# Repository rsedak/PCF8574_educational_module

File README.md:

[Croatian version](README_HR-HR.md).

Introduction
============

Purpose of PCF8574 educational module is student education.

Contributor
------------
- Robert Sedak — features, Arduino programming, schematic design, CAD design.

Application
-----------
Robert Sedak made a video with example programmed in Arduino IDE:

You can download example for Arduino IDE from [here](examples/).

Bill Of Materials
-----------------
- 1 ea., PCB
- 4 ea., 1K ohm 1/4W 1% Resistor (R1, R2, R3, R4)
- 3 ea., 10K ohm 1/4W 1% Resistor (R5, R6, R7)
- 2 ea., 4.7K ohm 1/4W 1% Resistor (R8, R9)
- 4 ea., LED 3mm (D1, D2, D3, D4)
- 4 ea., 6x6x4.3mm SPST Momentary push switch (SW1, SW2, SW3, SW4)
- 1 ea., 100nF 50V Monolithic Ceramic Capacitor
- 1 ea., 16-Pin DIL IC Socket
- 1 ea., PCF8574
- 1 ea., 1x5 pin 2.54mm Right Angle Pin Header (J1)
- 1 ea., 1x4 pin 2.54mm Socket Connector - Right angle (J2)
- 1 ea., 2x3 pin 2.54mm Straight Pin Header (J3)

Design Files
------------
This project is designed using Open Source [KiCad](http://kicad.org/). Design files are located in the [design_files](design_files/) folder.  You can see the [schematic](images/PCF8574_educational_module_schematic.png).

Gerber files
------------
You can download gerber files from [here](gerber/PCF8574_educational_module.zip).

Firmware
--------
This project can be programmed using the Open Source [Arduino](https://www.arduino.cc/).
Arduino example is located in [examples](examples/) folder.

License
-------
[Attribution-ShareAlike 4.0 International (CC BY-SA 4.0)](https://creativecommons.org/licenses/by-sa/4.0/)

You are free to:
- Share — copy and redistribute the material in any medium or format
- Adapt — remix, transform, and build upon the material

This license is acceptable for Free Cultural Works.
- The licensor cannot revoke these freedoms as long as you follow the license terms.

Under the following terms:
- Attribution — You must give appropriate credit, provide a link to the license, and indicate if changes were made. You may do so in any reasonable manner, but not in any way that suggests the licensor endorses you or your use.
- ShareAlike — If you remix, transform, or build upon the material, you must distribute your contributions under the same license as the original.

No additional restrictions — You may not apply legal terms or technological measures that legally restrict others from doing anything the license permits.

Reference Designs ARE PROVIDED "AS IS" AND "WITH ALL FAULTS". Authors DISCLAIMS ALL OTHER WARRANTIES, EXPRESS OR IMPLIED, REGARDING PRODUCTS, INCLUDING BUT NOT LIMITED TO, ANY IMPLIED WARRANTIES OF MERCHANTABILITY OR FITNESS FOR A PARTICULAR PURPOSE.
Authors may make changes to specifications and product descriptions at any time, without notice. The Customer must notrely on the absence or characteristics of any features or instructions marked "reserved" or "undefined."
Authors reservesthese for future definition and shall have no responsibility whatsoever for conflicts or incompatibilities arising from future changes to them. The product information on the Web Site or Materials is subject to change without notice. Do not finalize a design with this info.

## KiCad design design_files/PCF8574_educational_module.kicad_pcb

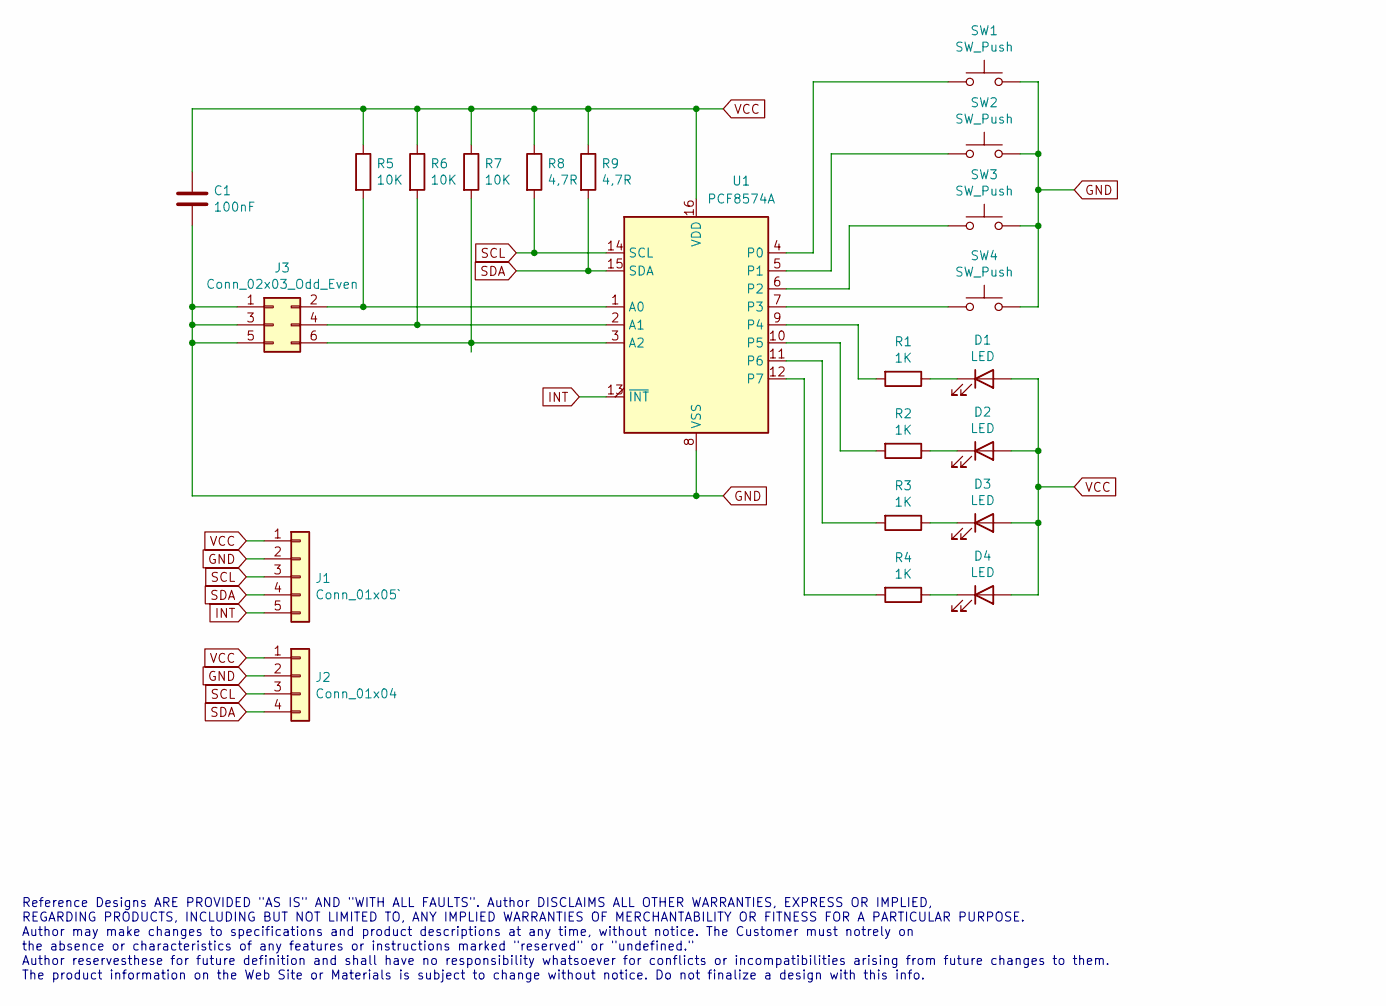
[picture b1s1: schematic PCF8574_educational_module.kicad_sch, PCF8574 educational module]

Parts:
C1: 100nF; C_Rect_L4.6mm_W2.0mm_P2.50mm_MKS02_FKP02
D1, D2, D3, D4: LED; LED_D3.0mm
J1: Conn_01x05`; PinHeader_1x05_P2.54mm_Horizontal
J2: Conn_01x04; PinSocket_1x04_P2.54mm_Horizontal
J3: Conn_02x03_Odd_Even; PinHeader_2x03_P2.54mm_Vertical
R1, R2, R3, R4: 1K; R_Axial_DIN0207_L6.3mm_D2.5mm_P7.62mm_Horizontal
R5, R6, R7: 10K; R_Axial_DIN0207_L6.3mm_D2.5mm_P7.62mm_Horizontal
R8, R9: 4,7R; R_Axial_DIN0207_L6.3mm_D2.5mm_P7.62mm_Horizontal
SW1, SW2, SW3, SW4: SW_Push; SW_PUSH_6mm
U1: PCF8574A; DIP-16_W7.62mm_Socket

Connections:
GND: C1.2, J1.2, J2.2, J3.1, J3.3, J3.5, SW1.2, SW2.2, SW3.2, SW4.2, U1.8 (VSS)
INT: J1.5, U1.13 (~INT)
unnamed: D1.1 (K), R1.1
unnamed: D2.1 (K), R2.1
unnamed: D3.1 (K), R3.1
unnamed: D4.1 (K), R4.1
unnamed: J3.2, R5.2, U1.1 (A0)
unnamed: J3.4, R6.2, U1.2 (A1)
unnamed: J3.6, R7.2, U1.3 (A2)
unnamed: R1.2, U1.9 (P4)
unnamed: R2.2, U1.10 (P5)
unnamed: R3.2, U1.11 (P6)
unnamed: R4.2, U1.12 (P7)
unnamed: SW1.1, U1.4 (P0)
unnamed: SW2.1, U1.5 (P1)
unnamed: SW3.1, U1.6 (P2)
unnamed: SW4.1, U1.7 (P3)
SCL: J1.3, J2.3, R8.2, U1.14 (SCL)
SDA: J1.4, J2.4, R9.2, U1.15 (SDA)
VCC: C1.1, D1.2 (A), D2.2 (A), D3.2 (A), D4.2 (A), J1.1, J2.1, R5.1, R6.1, R7.1, R8.1, R9.1, U1.16 (VDD)

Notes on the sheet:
Reference Designs ARE PROVIDED "AS IS" AND "WITH ALL FAULTS". Author DISCLAIMS ALL OTHER WARRANTIES, EXPRESS OR IMPLIED, REGARDING PRODUCTS, INCLUDING BUT NOT LIMITED TO, ANY IMPLIED WARRANTIES OF MERCHANTABILITY OR FITNESS FOR A PARTICULAR PURPOSE. Author may make changes to specifications and pro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

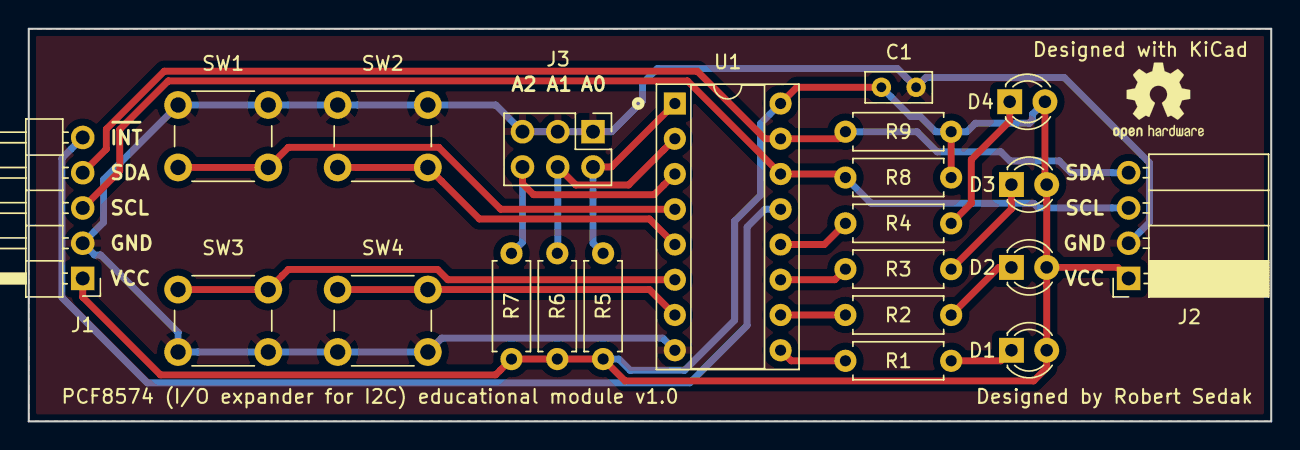
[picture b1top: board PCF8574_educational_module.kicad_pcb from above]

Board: 2 copper layers, 89.5 x 28.3 mm, 22 parts (0 on the bottom side), 20 nets.

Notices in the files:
design_files/PCF8574_educational_module.kicad_pcb:
License: CC-BY-SA 4.0
